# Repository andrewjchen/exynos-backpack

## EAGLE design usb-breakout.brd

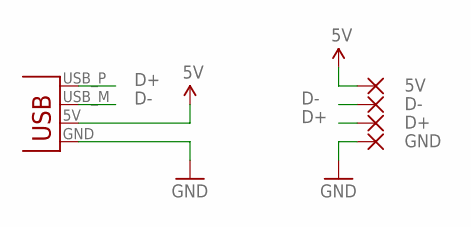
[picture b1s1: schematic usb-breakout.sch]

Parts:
JP1: USBPCB; USB-A-PCB
PAD1: GND; 5-1,8
PAD2: D+; 5-1,8
PAD3: D-; 5-1,8
PAD4: 5V; 5-1,8

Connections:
5V: JP1.5V (VBUS), PAD4.1
D+: JP1.USB_P (D+), PAD2.1
D-: JP1.USB_M (D-), PAD3.1
GND: JP1.GND, PAD1.1

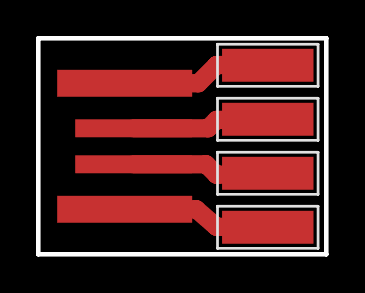
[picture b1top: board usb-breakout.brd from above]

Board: 2 copper layers, 16.0 x 12.0 mm, 5 parts (0 on the bottom side), 4 nets.

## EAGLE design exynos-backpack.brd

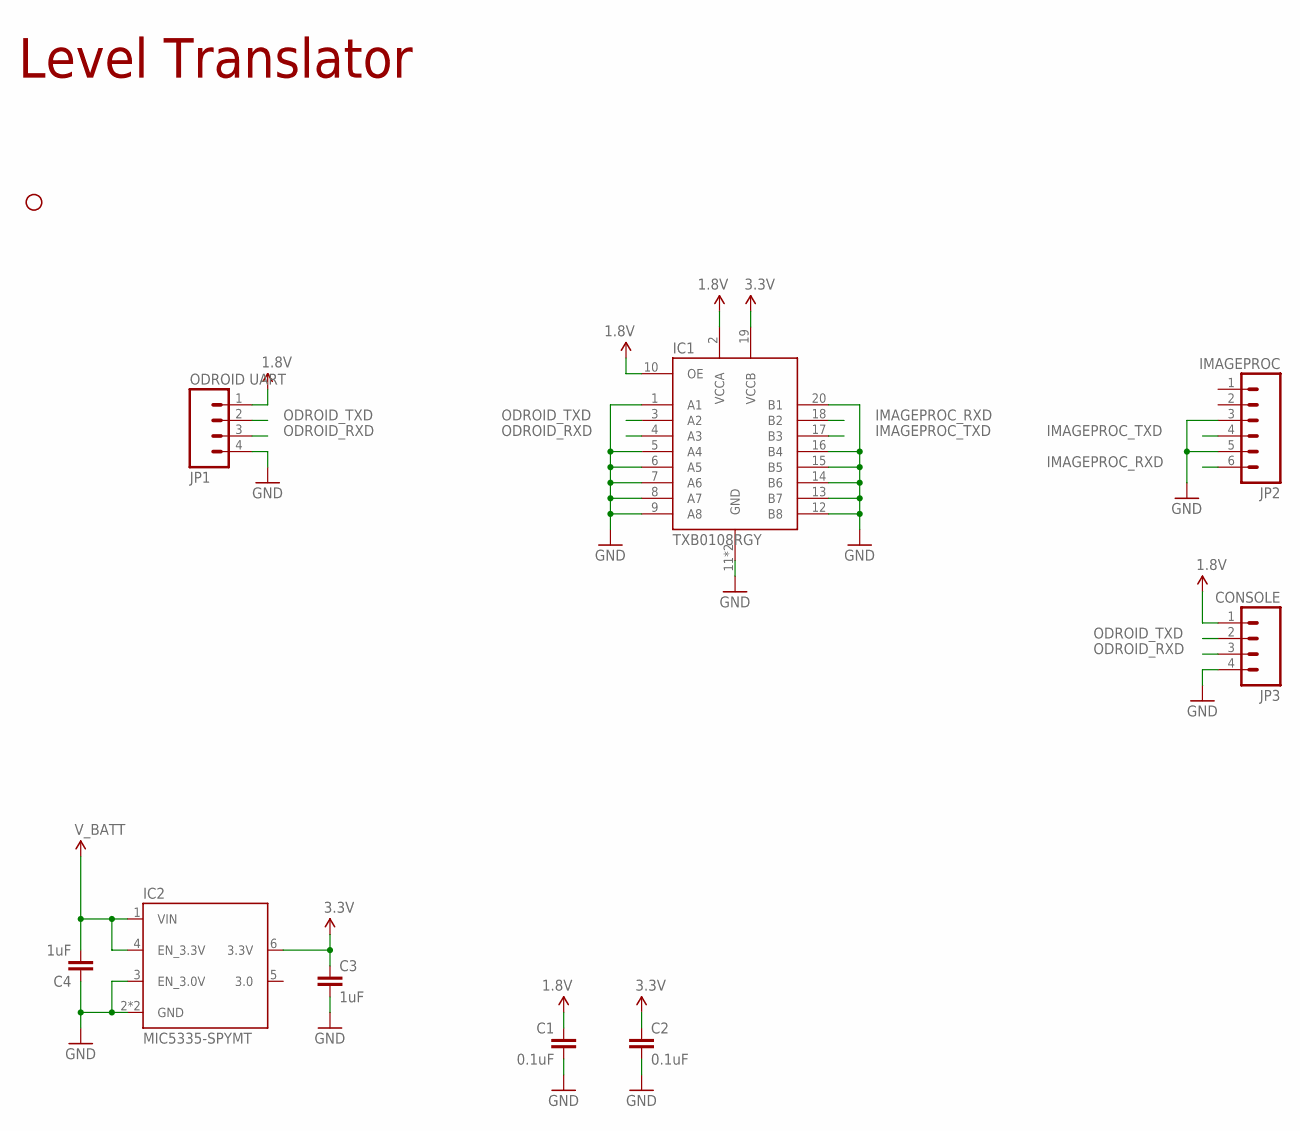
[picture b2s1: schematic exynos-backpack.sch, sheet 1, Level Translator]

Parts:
C1, C2: 0.1uF; 0402-CAP
C3, C4: 1uF; 0402-CAP
IC1: TXB0108RGY; R-PVQFN-N20
IC2: MIC5335-SPYMT; MLF-6
JP1: ODROID UART; 1X04_MOLEX_5267_NOSILK
JP2: IMAGEPROC; MOLEX_503480-0600
JP3: CONSOLE; 1X04_MOLEX_5267
U$2: ODROID-U2; ODROID-U2-KEEPOUT

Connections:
1.8V: C1.1, IC1.2 (VCCA), IC1.10 (OE), JP1.1, JP3.1
3.3V: C2.1, C3.1, IC1.19 (VCCB), IC2.6 (3.3V)
GND: C1.2, C2.2, C3.2, C4.1, IC1.1 (A1), IC1.5 (A4), IC1.6 (A5), IC1.7 (A6), IC1.8 (A7), IC1.9 (A8), IC1.11 (GND), IC1.12 (B8), IC1.13 (B7), IC1.14 (B6), IC1.15 (B5), IC1.16 (B4), IC1.20 (B1), IC1.EPAD (GND), IC2.2 (GND), IC2.3 (EN_3.0V), IC2.EPAD (GND), JP1.4, JP2.3, JP2.5, JP3.4; also elsewhere on the board
IMAGEPROC_RXD: IC1.18 (B2), JP2.6
IMAGEPROC_TXD: IC1.17 (B3), JP2.4
ODROID_RXD: IC1.4 (A3), JP1.3, JP3.3
ODROID_TXD: IC1.3 (A2), JP1.2, JP3.2
V_BATT: C4.2, IC2.1 (VIN), IC2.4 (EN_3.3V); also elsewhere on the board

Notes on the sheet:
Level Translator

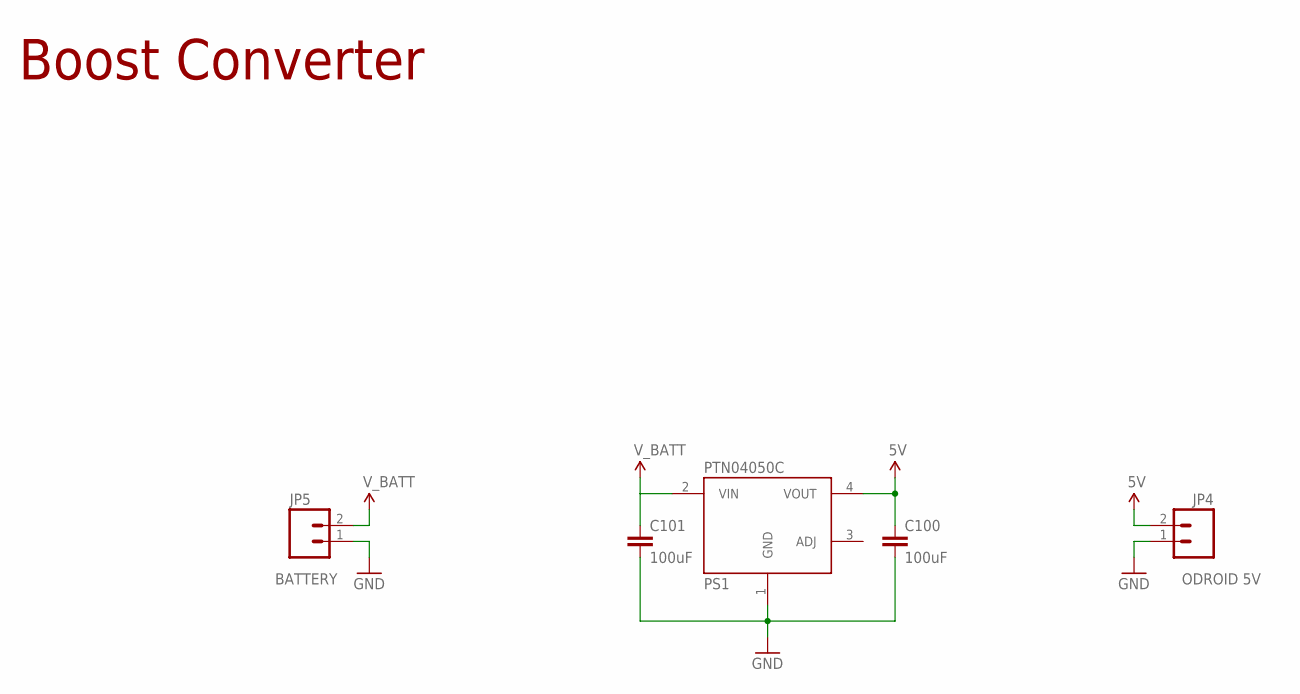
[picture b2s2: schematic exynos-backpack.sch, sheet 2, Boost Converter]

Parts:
C100, C101: 100uF; 1210
JP4: ODROID 5V; JST-RCY-FEMALE_NOSILK
JP5: BATTERY; JST-RCY-MALE_NOSILK
PS1: PTN04050C

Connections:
5V: C100.1, JP4.2, PS1.4 (VOUT)
GND: C100.2, C101.2, JP4.1, JP5.1, PS1.1 (GND); also elsewhere on the board
V_BATT: C101.1, JP5.2, PS1.2 (VIN); also elsewhere on the board

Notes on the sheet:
Boost Converter

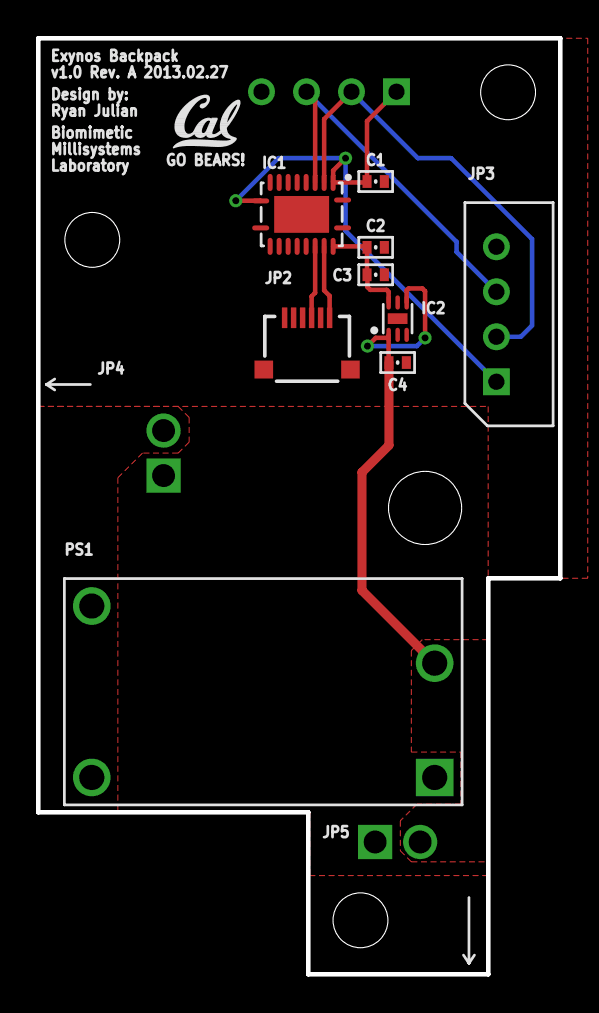
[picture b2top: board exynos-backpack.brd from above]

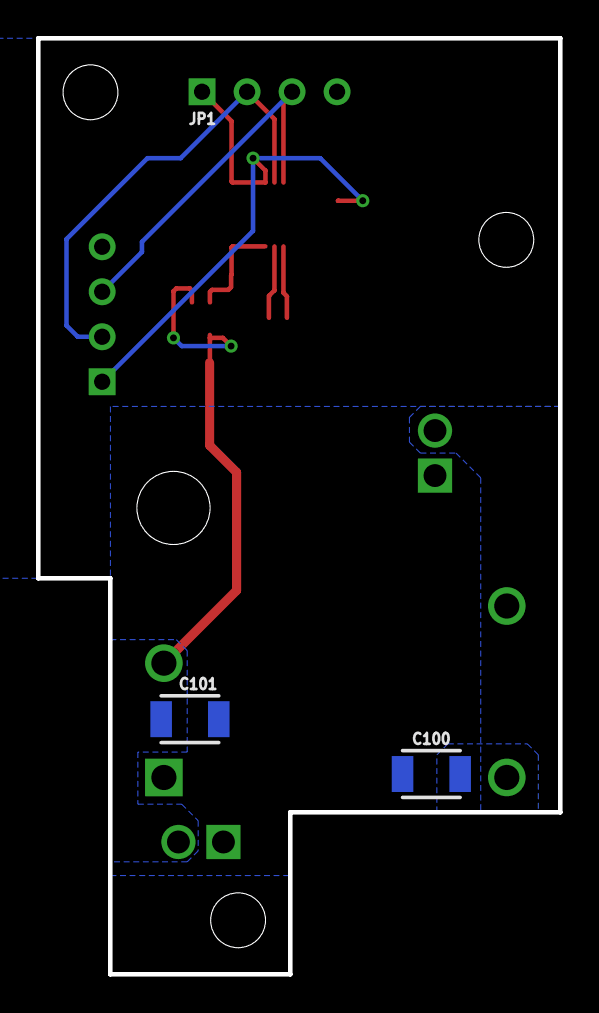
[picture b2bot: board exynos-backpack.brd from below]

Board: 4 copper layers, 29.0 x 52.0 mm, 16 parts (2 on the bottom side), 9 nets.

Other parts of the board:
$$U$1: CAL_LOGO

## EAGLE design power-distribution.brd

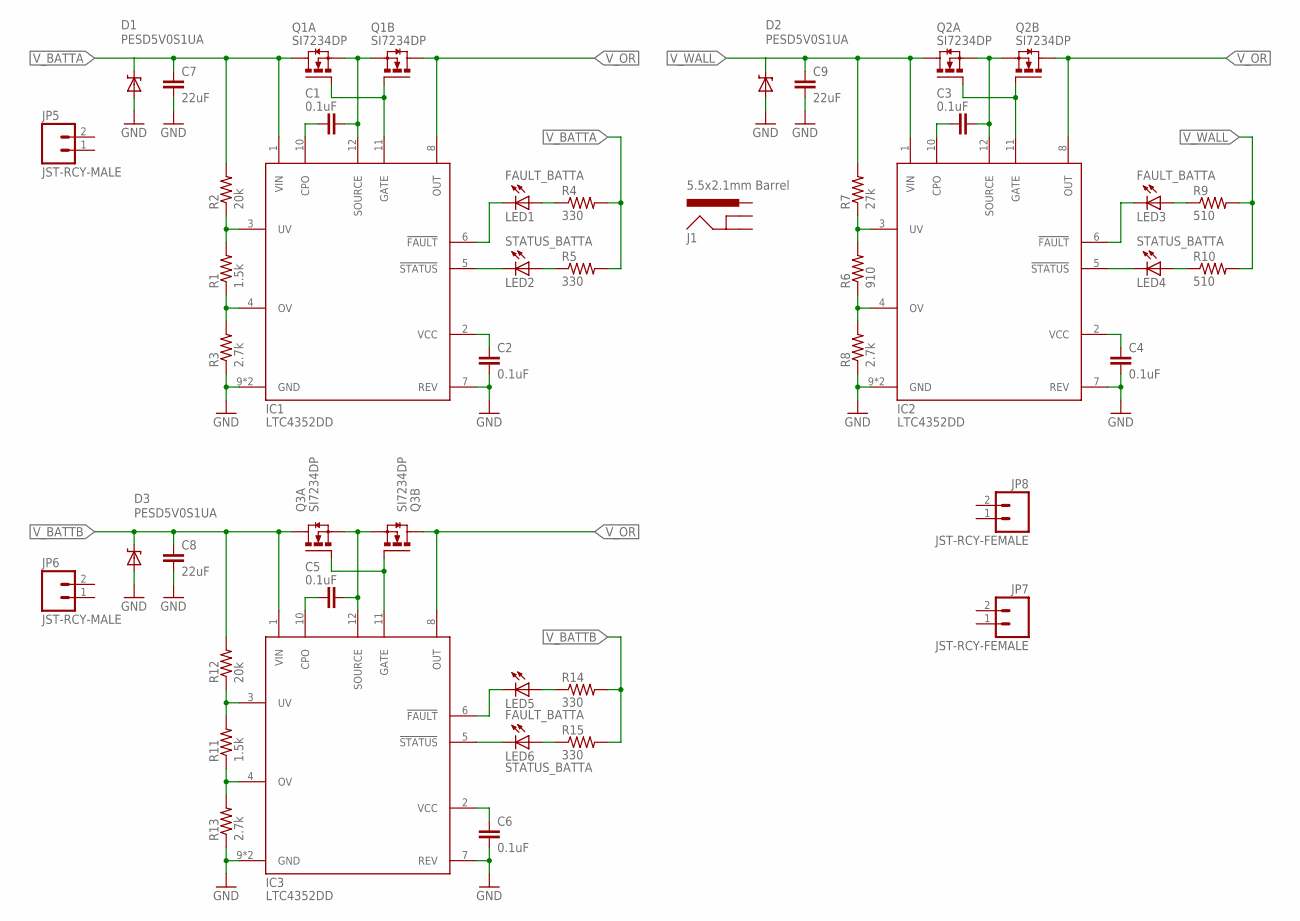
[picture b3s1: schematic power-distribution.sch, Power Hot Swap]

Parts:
C1, C2, C3, C4, C5, C6: 0.1uF; 0402-CAP
C7, C8, C9: 22uF; 0603-CAP
D1, D2, D3: PESD5V0S1UA; SOD-323
IC1, IC2, IC3: LTC4352DD; DFN-12-3X3-DD
J1: 5.5x2.1mm Barrel; POWER_JACK_SMD
JP5, JP6: JST-RCY-MALE
JP7, JP8: JST-RCY-FEMALE
LED1, LED3, LED5: FAULT_BATTA; LED-0603
LED2, LED4, LED6: STATUS_BATTA; LED-0603
Q1, Q2, Q3: SI7234DP; POWERPAK-SO-8-DUAL
R1, R11: 1.5k; 0402-RES
R2, R12: 20k; 0402-RES
R3, R8, R13: 2.7k; 0402-RES
R4, R5, R14, R15: 330; 0402-RES
R6: 910; 0402-RES
R7: 27k; 0402-RES
R9, R10: 510; 0402-RES

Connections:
GND: C2.2, C4.2, C6.2, C7.2, C8.2, C9.2, D1.2 (A), D2.2 (A), D3.2 (A), IC1.7 (REV), IC1.9 (GND), IC1.PAD (GND), IC2.7 (REV), IC2.9 (GND), IC2.PAD (GND), IC3.7 (REV), IC3.9 (GND), IC3.PAD (GND), R3.1, R8.1, R13.1
unnamed: C1.2, IC1.12 (SOURCE), Q1.1 (S), Q1.3 (S)
unnamed: IC1.11 (GATE), Q1.2 (G), Q1.4 (G)
unnamed: C1.1, IC1.10 (CPO)
unnamed: IC1.3 (UV), R1.2, R2.1
unnamed: IC1.4 (OV), R1.1, R3.2
unnamed: C2.1, IC1.2 (VCC)
unnamed: IC1.6 (!FAULT), LED1.C
unnamed: IC1.5 (!STATUS), LED2.C
unnamed: LED2.A, R5.1
unnamed: LED1.A, R4.1
unnamed: C3.2, IC2.12 (SOURCE), Q2.1 (S), Q2.3 (S)
unnamed: IC2.11 (GATE), Q2.2 (G), Q2.4 (G)
unnamed: C3.1, IC2.10 (CPO)
unnamed: IC2.3 (UV), R6.2, R7.1
unnamed: IC2.4 (OV), R6.1, R8.2
unnamed: C4.1, IC2.2 (VCC)
unnamed: IC2.6 (!FAULT), LED3.C
unnamed: IC2.5 (!STATUS), LED4.C
unnamed: LED4.A, R10.1
unnamed: LED3.A, R9.1
unnamed: C5.2, IC3.12 (SOURCE), Q3.1 (S), Q3.3 (S)
unnamed: IC3.11 (GATE), Q3.2 (G), Q3.4 (G)
unnamed: C5.1, IC3.10 (CPO)
unnamed: IC3.3 (UV), R11.2, R12.1
unnamed: IC3.4 (OV), R11.1, R13.2
unnamed: C6.1, IC3.2 (VCC)
unnamed: IC3.6 (!FAULT), LED5.C
unnamed: IC3.5 (!STATUS), LED6.C
unnamed: LED6.A, R15.1
unnamed: LED5.A, R14.1
V_BATTA: C7.1, D1.1 (C), IC1.1 (VIN), Q1.7+8 (D), R2.2, R4.2, R5.2
V_BATTB: C8.1, D3.1 (C), IC3.1 (VIN), Q3.7+8 (D), R12.2, R14.2, R15.2
V_OR: IC1.8 (OUT), IC2.8 (OUT), IC3.8 (OUT), Q1.5+6 (D), Q2.5+6 (D), Q3.5+6 (D)
V_WALL: C9.1, D2.1 (C), IC2.1 (VIN), Q2.7+8 (D), R7.2, R9.2, R10.2

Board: 4 copper layers, 45 parts (34 on the bottom side), 35 nets, no tracks yet.

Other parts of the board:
U$12: CAL_LOGO

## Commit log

2013-02-14 Initial commit with partial schematic and SPICE
2013-02-14 Make single model LTC4352 SPICE for easier testing
2013-02-14 Use VBATT instead of Vout for LEDs in min model
2013-02-15 Update MOSFETs to Si7234DP in SPICE
2013-02-15 Add ODROID-U2 drawing
2013-02-15 Add TVS protection diodes
2013-02-15 Add boost converter
2013-02-16 Unswap OV/UV resistors
2013-02-16 Reduce current-limiting resistor values
2013-02-16 Adjust Rlim on LiPo ideal-OR LEDs down to 330
2013-02-16 Change OV/UV resistors to Robert Ou's values
2013-02-17 Rearrange LED circuits in schematic
2013-02-18 Add JST connectors
2013-02-20 Add incomplete ODROID-U2 template
2013-02-21 Complete first draft of ODROID-U2 template
2013-02-23 Update footprint to avoid connectors
2013-02-25 More work on backpack placement
2013-02-25 Split power distribution into its own PCB
2013-02-26 First pass at exynos backpack placement
2013-02-26 Finish placement
2013-02-27 Revise footprint for correct ethernet connector size
2013-02-27 Add hole for encoder cable
2013-02-27 Revise placement for new dimension
2013-02-27 Route serial section
2013-02-27 Routing complete
2013-02-27 Arrange silkscreen
2013-02-27 Disable 3.0v supply
2013-02-27 Renumber components for silk
2013-02-27 Fix via overlap with silk
2013-02-28 Add USB breakout board

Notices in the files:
parts and their libraries:
biomimetic: UC Regents. All rights reserved.
SparkFun-Connectors: Licensing: CC v3.0 Share-Alike You are welcome to use this library for commercial purposes.
